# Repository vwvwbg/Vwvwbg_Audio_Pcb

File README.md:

# Vwvwbg_Audio_Pcb
Eagle PCB Project &amp; Gerber

some modified edition for Kevin Gilmore's design and some simple design by me

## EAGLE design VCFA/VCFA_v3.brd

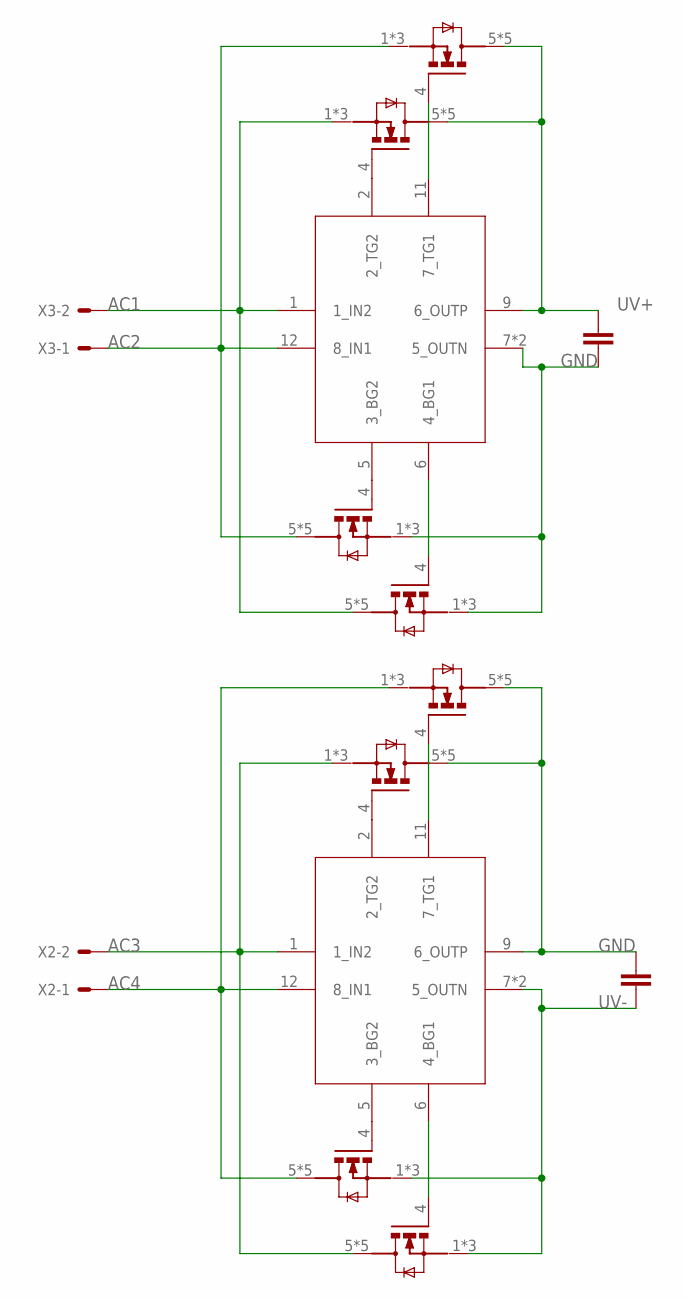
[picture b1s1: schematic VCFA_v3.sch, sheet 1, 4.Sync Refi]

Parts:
C57, C59: 47uF; C1206
Q97, Q98, Q99, Q100, Q105, Q106, Q107, Q108: MOS_SMDTDSON-8; PG-TDSON-8
U$2, U$4: LT4320MSOP; LT4320_MSOP
X2, X3: KK-156-2

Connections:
AC1: Q97.1 (S), Q97.2 (S), Q97.3 (S), Q100.5 (D), Q100.6 (D), Q100.7 (D), Q100.8 (D), Q100.TH (D), U$2.1 (1_IN2), X3.2
AC2: Q98.1 (S), Q98.2 (S), Q98.3 (S), Q99.5 (D), Q99.6 (D), Q99.7 (D), Q99.8 (D), Q99.TH (D), U$2.12 (8_IN1), X3.1
AC3: Q105.1 (S), Q105.2 (S), Q105.3 (S), Q108.5 (D), Q108.6 (D), Q108.7 (D), Q108.8 (D), Q108.TH (D), U$4.1 (1_IN2), X2.2
AC4: Q106.1 (S), Q106.2 (S), Q106.3 (S), Q107.5 (D), Q107.6 (D), Q107.7 (D), Q107.8 (D), Q107.TH (D), U$4.12 (8_IN1), X2.1
GND: C57.2, C59.1, Q99.1 (S), Q99.2 (S), Q99.3 (S), Q100.1 (S), Q100.2 (S), Q100.3 (S), Q105.5 (D), Q105.6 (D), Q105.7 (D), Q105.8 (D), Q105.TH (D), Q106.5 (D), Q106.6 (D), Q106.7 (D), Q106.8 (D), Q106.TH (D), U$2.7 (5_OUTN), U$2.EXP (5_OUTN), U$4.9 (6_OUTP); also elsewhere on the board
unnamed: Q98.4 (G), U$2.11 (7_TG1)
unnamed: Q100.4 (G), U$2.6 (4_BG1)
unnamed: Q97.4 (G), U$2.2 (2_TG2)
unnamed: Q99.4 (G), U$2.5 (3_BG2)
unnamed: Q106.4 (G), U$4.11 (7_TG1)
unnamed: Q108.4 (G), U$4.6 (4_BG1)
unnamed: Q105.4 (G), U$4.2 (2_TG2)
unnamed: Q107.4 (G), U$4.5 (3_BG2)
UV+: C57.1, Q97.5 (D), Q97.6 (D), Q97.7 (D), Q97.8 (D), Q97.TH (D), Q98.5 (D), Q98.6 (D), Q98.7 (D), Q98.8 (D), Q98.TH (D), U$2.9 (6_OUTP); also elsewhere on the board
UV-: C59.2, Q107.1 (S), Q107.2 (S), Q107.3 (S), Q108.1 (S), Q108.2 (S), Q108.3 (S), U$4.7 (5_OUTN), U$4.EXP (5_OUTN); also elsewhere on the board

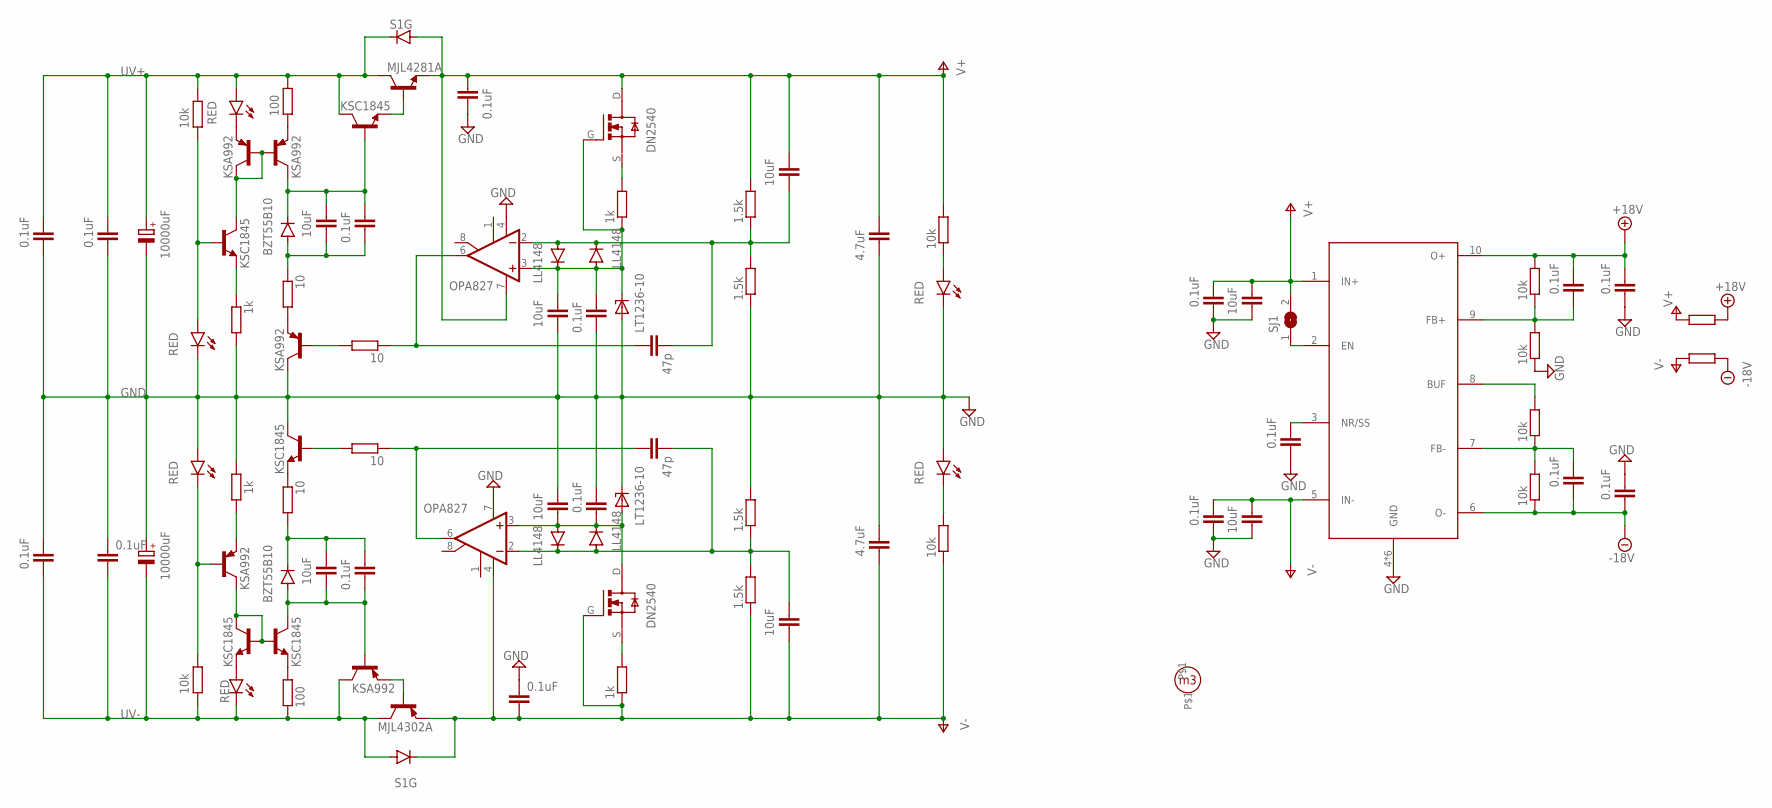
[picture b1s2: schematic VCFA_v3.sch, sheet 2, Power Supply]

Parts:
C2, C43, C44, C45, C46, C49, C50, C67, C68, C69, C70, C71, C72: 0.1uF; C0805
C37, C38: 10000uF; EB35D-8.5
C39, C42, C58, C60: 0.1uF; C050-045X075
C40, C41, C47, C48, C53, C54, C65, C66: 10uF; C1206
C51, C52: 47p; C0805
C55, C56: 4.7uF; C050-075X075
D13, D14: BZT55B10; SOD80C
D15, D16: S1G; DO214AA
D17, D18: LT1236-10; SO8
D19, D20, D21, D22: LL4148; SOD80C
H8: HOLE; M3_HOLE
IC5, IC6: OPA827; SOIC8
LED13, LED14, LED15, LED16, LED17, LED18: RED; LED_SML1206
Q79, Q82, Q84, Q86, Q87: KSC1845; TRANSISTOR_TO92-ECB_N
Q80, Q81, Q83, Q85, Q88: KSA992; TRANSISTOR_TO92-ECB_P
Q89: MJL4281A; TRANSISTOR_TO247_BCE_N
Q90: MJL4302A; TRANSISTOR_TO247_BCE_P
Q91, Q92: DN2540; TRANSISTOR_TO92-SGD_N
R115, R116, R131, R132, R136, R137, R138, R139, R140, R141: 10k; MINI_MELF-0204W
R117, R118, R125, R126: 1k; MINI_MELF-0204W
R119, R122: 100; MINI_MELF-0204W
R120, R121, R123, R124: 10; MINI_MELF-0204W
R127, R128, R129, R130: 1.5k; MINI_MELF-0204W
SJ1: SJ
U$5: TPS7A39WSON10-7A39; SON50P300X300X80-11T165X240N

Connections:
+18V: C69.1, C71.1, R136.2, R141.1, U$5.10 (O+); also elsewhere on the board
-18V: C70.2, C72.2, R139.1, R140.1, U$5.6 (O-); also elsewhere on the board
GND: C2.2, C37.-, C38.+, C39.2, C42.1, C45.1, C46.2, C47.2, C48.1, C49.2, C50.1, C55.1, C56.2, C58.1, C60.2, C65.2, C66.2, C67.2, C68.2, C69.2, C70.1, D17.4 (GND), D18.6 (OUT), IC5.7 (V+), IC6.4 (V-), LED13.C, LED14.A, LED17.C, LED18.A, Q85.C, Q86.C, R117.2, R118.1, R128.1, R129.2, R137.1, U$5.4 (GND), U$5.11 (GND), U$5.12 (GND), U$5.13 (GND), U$5.14 (GND), U$5.15 (GND); also elsewhere on the board
unnamed: Q79.C, Q81.B, Q81.C, Q83.B
unnamed: SJ1.1, U$5.2 (EN)
unnamed: LED15.C, Q81.E
unnamed: Q83.E, R119.2
unnamed: C40.1, C43.1, D13.C, Q83.C, Q87.B
unnamed: C40.2, C43.2, D13.A, R120.1
unnamed: Q85.E, R120.2
unnamed: Q79.E, R117.1
unnamed: LED13.A, Q79.B, R115.2
unnamed: Q80.E, R118.2
unnamed: LED14.C, Q80.B, R116.1
unnamed: Q86.E, R121.1
unnamed: C41.1, C44.1, D14.C, R121.2
unnamed: C41.2, C44.2, D14.A, Q84.C, Q88.B
unnamed: Q80.C, Q82.B, Q82.C, Q84.B
unnamed: Q84.E, R122.1
unnamed: LED16.A, Q82.E
unnamed: Q88.E, Q90.B
unnamed: Q87.E, Q89.B
unnamed: C51.1, IC6.6 (OUT), R123.1
unnamed: C52.1, IC5.6 (OUT), R124.1
unnamed: Q86.B, R124.2
unnamed: Q85.B, R123.2
unnamed: C51.2, C53.2, D19.A, D20.C, IC6.2 (-IN), R127.1, R128.2
unnamed: C47.1, C49.1, D17.6 (OUT), D19.C, D20.A, IC6.3 (+IN), Q91.G, R125.1
unnamed: Q91.S, R125.2
unnamed: C48.2, C50.2, D18.4 (GND), D21.A, D22.C, IC5.3 (+IN), Q92.D
unnamed: Q92.S, R126.2
unnamed: C52.2, C54.1, D21.C, D22.A, IC5.2 (-IN), R129.1, R130.2
unnamed: LED18.C, R132.2
unnamed: LED17.A, R131.1
unnamed: C72.1, R138.1, R139.2, U$5.7 (FB-)
unnamed: R138.2, U$5.8 (BUF)
unnamed: C71.2, R136.1, R137.2, U$5.9 (FB+)
unnamed: C2.1, U$5.3 (NR/SS)
UV+: C37.+, C42.2, C58.2, D15.C, LED15.A, Q87.C, Q89.C, R115.1, R119.1; also elsewhere on the board
UV-: C38.-, C39.1, C60.1, D16.A, LED16.C, Q88.C, Q90.C, R116.2, R122.2; also elsewhere on the board
V+: C45.2, C53.1, C55.2, C66.1, C68.1, D15.A, IC6.7 (V+), Q89.E, Q91.D, R127.2, R131.2, R141.2, SJ1.2, U$5.1 (IN+); also elsewhere on the board
V-: C46.1, C54.2, C56.1, C65.1, C67.1, D16.C, IC5.4 (V-), Q90.E, Q92.G, R126.1, R130.1, R132.1, R140.2, U$5.5 (IN-); also elsewhere on the board

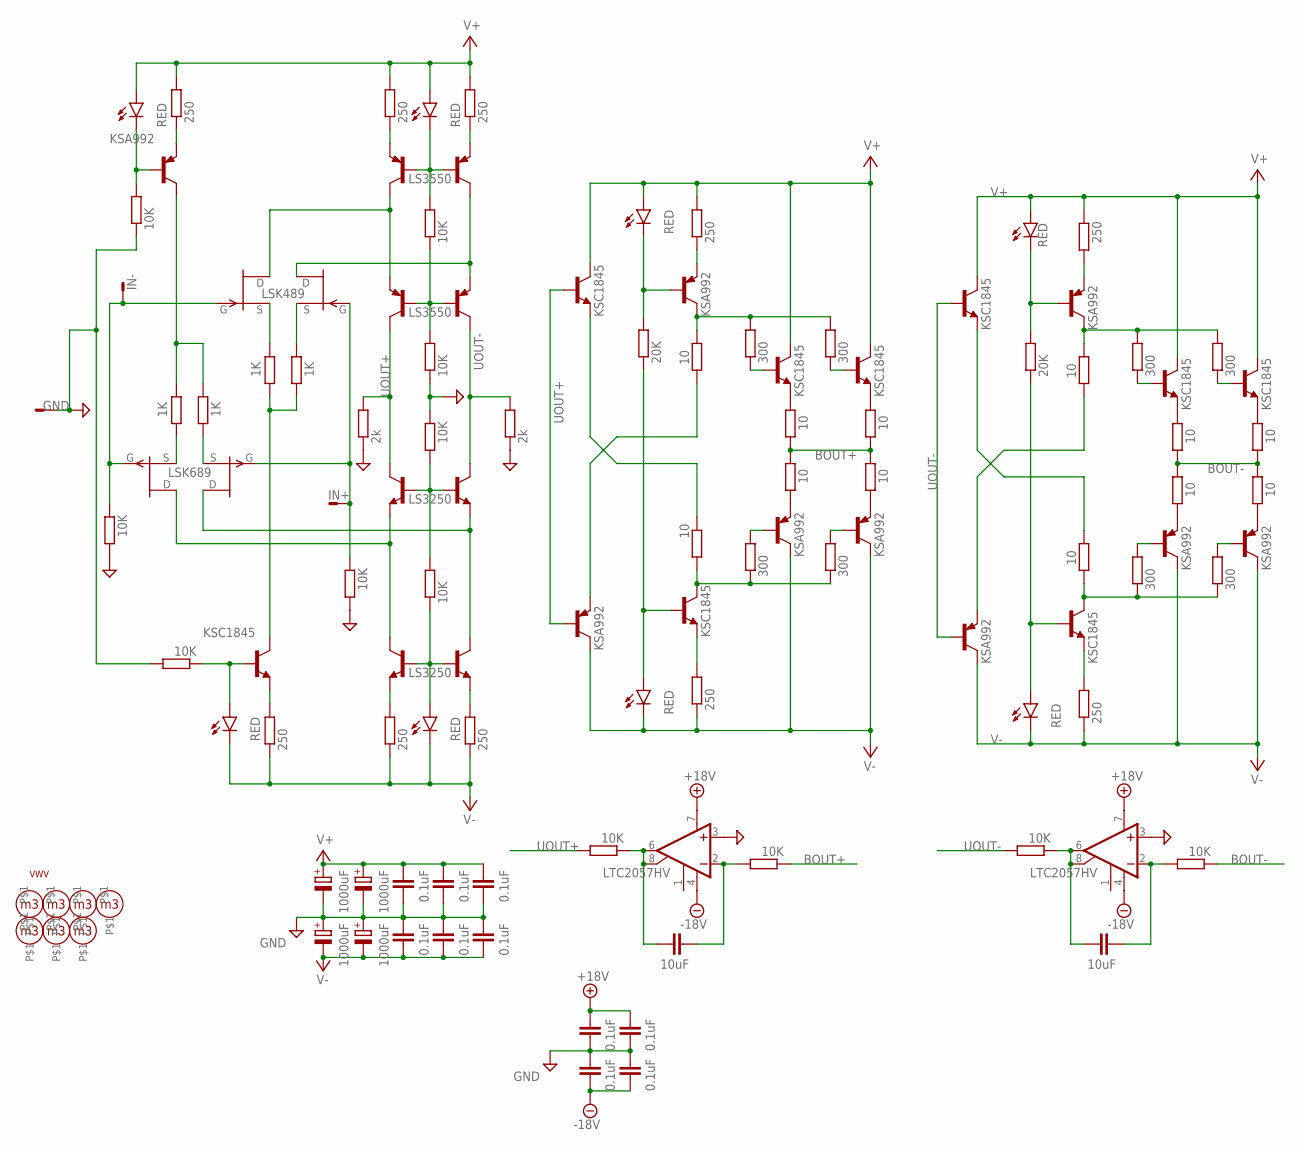
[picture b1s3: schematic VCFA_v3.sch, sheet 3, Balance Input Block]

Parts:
C3, C4, C14, C15: 0.1uF; C0805
C5, C6, C7, C8: 1000uF; E7,5-18
C9, C10, C11, C12, C74, C75: 0.1uF; C050-045X075
C13, C16: 10uF; C1206
H1, H2, H3, H4, H5, H6, H7: HOLE; M3_HOLE
IC1, IC2: LTC2057HV; SOIC8
LED1, LED2, LED3, LED4, LED5, LED6, LED7, LED8: RED; LED_SML1206
Q1: LSK689; SOT-23-6
Q2, Q10, Q11, Q14, Q16, Q18, Q19, Q22, Q24: KSA992; TRANSISTOR_TO92-ECB_P
Q3, Q9, Q12, Q13, Q15, Q17, Q20, Q21, Q23: KSC1845; TRANSISTOR_TO92-ECB_N
Q4: LSK489; SOT-23-6
Q5, Q8: LS3550; SOT-23-6
Q6, Q7: LS3250; SOT-23-6
R3, R4, R14, R15, R16, R17, R21, R29, R36, R44, R134, R135: 10K; MINI_MELF-0204W
R5, R7, R12, R13, R18, R19, R23, R26, R38, R41: 250; MINI_MELF-0204W
R6, R8, R9, R10: 1K; MINI_MELF-0204W
R11, R20: 2k; MINI_MELF-0204W
R22, R37: 20K; MINI_MELF-0204W
R24, R25, R30, R31, R34, R35, R39, R40, R45, R46, R49, R50: 10; MINI_MELF-0204W
R27, R28, R32, R33, R42, R43, R47, R48: 300; MINI_MELF-0204W
S1: VWV
X1: KK-156-3

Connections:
+18V: C3.2, C14.2, IC1.7 (V+), IC2.7 (V+); also elsewhere on the board
-18V: C4.1, C15.1, IC1.4 (V-), IC2.4 (V-); also elsewhere on the board
BOUT+: R29.1, R30.1, R31.2, R34.1, R35.2; also elsewhere on the board
BOUT-: R44.1, R45.1, R46.2, R49.1, R50.2; also elsewhere on the board
GND: C3.1, C4.2, C5.-, C6.+, C7.-, C8.+, C9.2, C10.1, C11.2, C12.1, C14.1, C15.2, C74.2, C75.1, IC1.3 (+IN), IC2.3 (+IN), R3.1, R4.2, R11.1, R15.1, R16.2, R20.1, R134.1, R135.1, X1.2; also elsewhere on the board
IN+: Q1.4 (G), Q4.4 (G), R134.2, X1.3
IN-: Q1.1 (G), Q4.1 (G), R135.2, X1.1
unnamed: Q8.2 (E), R12.1
unnamed: Q10.E, R24.2
unnamed: Q12.E, R26.2
unnamed: Q11.E, R23.1
unnamed: LED5.C, Q11.B, R22.2
unnamed: LED6.A, Q12.B, R22.1
unnamed: Q11.C, R24.1, R27.2, R32.2
unnamed: Q12.C, R25.2, R28.1, R33.1
unnamed: Q9.E, R25.1
unnamed: Q13.B, R27.1
unnamed: Q13.E, R30.2
unnamed: Q16.B, R33.2
unnamed: Q15.B, R32.1
unnamed: Q14.B, R28.2
unnamed: Q14.E, R31.1
unnamed: C13.2, IC1.2 (-IN), R29.2
unnamed: Q15.E, R34.2
unnamed: Q16.E, R35.1
unnamed: C13.1, IC1.6 (OUT), IC1.8 (CMP2), R21.1
unnamed: Q8.5 (E), R18.1
unnamed: Q20.E, R41.2
unnamed: Q19.E, R38.1
unnamed: LED7.C, Q19.B, R37.2
unnamed: LED8.A, Q20.B, R37.1
unnamed: Q19.C, R39.1, R42.2, R47.2
unnamed: Q20.C, R40.2, R43.1, R48.1
unnamed: Q18.E, R39.2
unnamed: Q17.E, R40.1
unnamed: Q21.B, R42.1
unnamed: Q22.B, R43.2
unnamed: Q23.B, R47.1
unnamed: Q24.B, R48.2
unnamed: Q21.E, R45.2
unnamed: Q22.E, R46.1
unnamed: Q23.E, R49.2
unnamed: Q24.E, R50.1
unnamed: C16.2, IC2.2 (-IN), R44.2
unnamed: C16.1, IC2.6 (OUT), IC2.8 (CMP2), R36.1
unnamed: Q7.5 (E), R13.2
unnamed: Q7.2 (E), R19.2
unnamed: Q1.5 (D), Q6.2 (E), Q7.4 (C)
unnamed: Q1.2 (D), Q6.5 (E), Q7.6 (C)
unnamed: LED4.A, Q7.1 (B), Q7.3 (B), R17.1
unnamed: Q6.1 (B), Q6.3 (B), R16.1, R17.2
unnamed: LED2.A, Q3.B, R4.1
unnamed: Q5.1 (B), Q5.3 (B), R14.1, R15.2
unnamed: Q4.2 (D), Q5.5 (E), Q8.4 (C)
unnamed: LED3.C, Q8.1 (B), Q8.3 (B), R14.2
unnamed: Q4.5 (D), Q5.2 (E), Q8.6 (C)
unnamed: LED1.C, Q2.B, R3.2
unnamed: Q2.E, R5.1
unnamed: Q2.C, R6.2, R8.2
unnamed: Q1.6 (S), R8.1
unnamed: Q1.3 (S), R6.1
unnamed: Q4.3 (S), R9.2
unnamed: Q4.6 (S), R10.2
unnamed: Q3.C, R9.1, R10.1
unnamed: Q3.E, R7.2
UOUT+: Q5.6 (C), Q6.6 (C), Q9.B, Q10.B, R11.2, R21.2
UOUT-: Q5.4 (C), Q6.4 (C), Q17.B, Q18.B, R20.2, R36.2
V+: C5.+, C7.+, C9.1, C11.1, C74.1, LED1.A, LED3.A, LED5.A, LED7.A, Q9.C, Q13.C, Q15.C, Q17.C, Q21.C, Q23.C, R5.2, R12.2, R18.2, R23.2, R38.2; also elsewhere on the board
V-: C6.-, C8.-, C10.2, C12.2, C75.2, LED2.C, LED4.C, LED6.C, LED8.C, Q10.C, Q14.C, Q16.C, Q18.C, Q22.C, Q24.C, R7.1, R13.1, R19.1, R26.1, R41.1; also elsewhere on the board

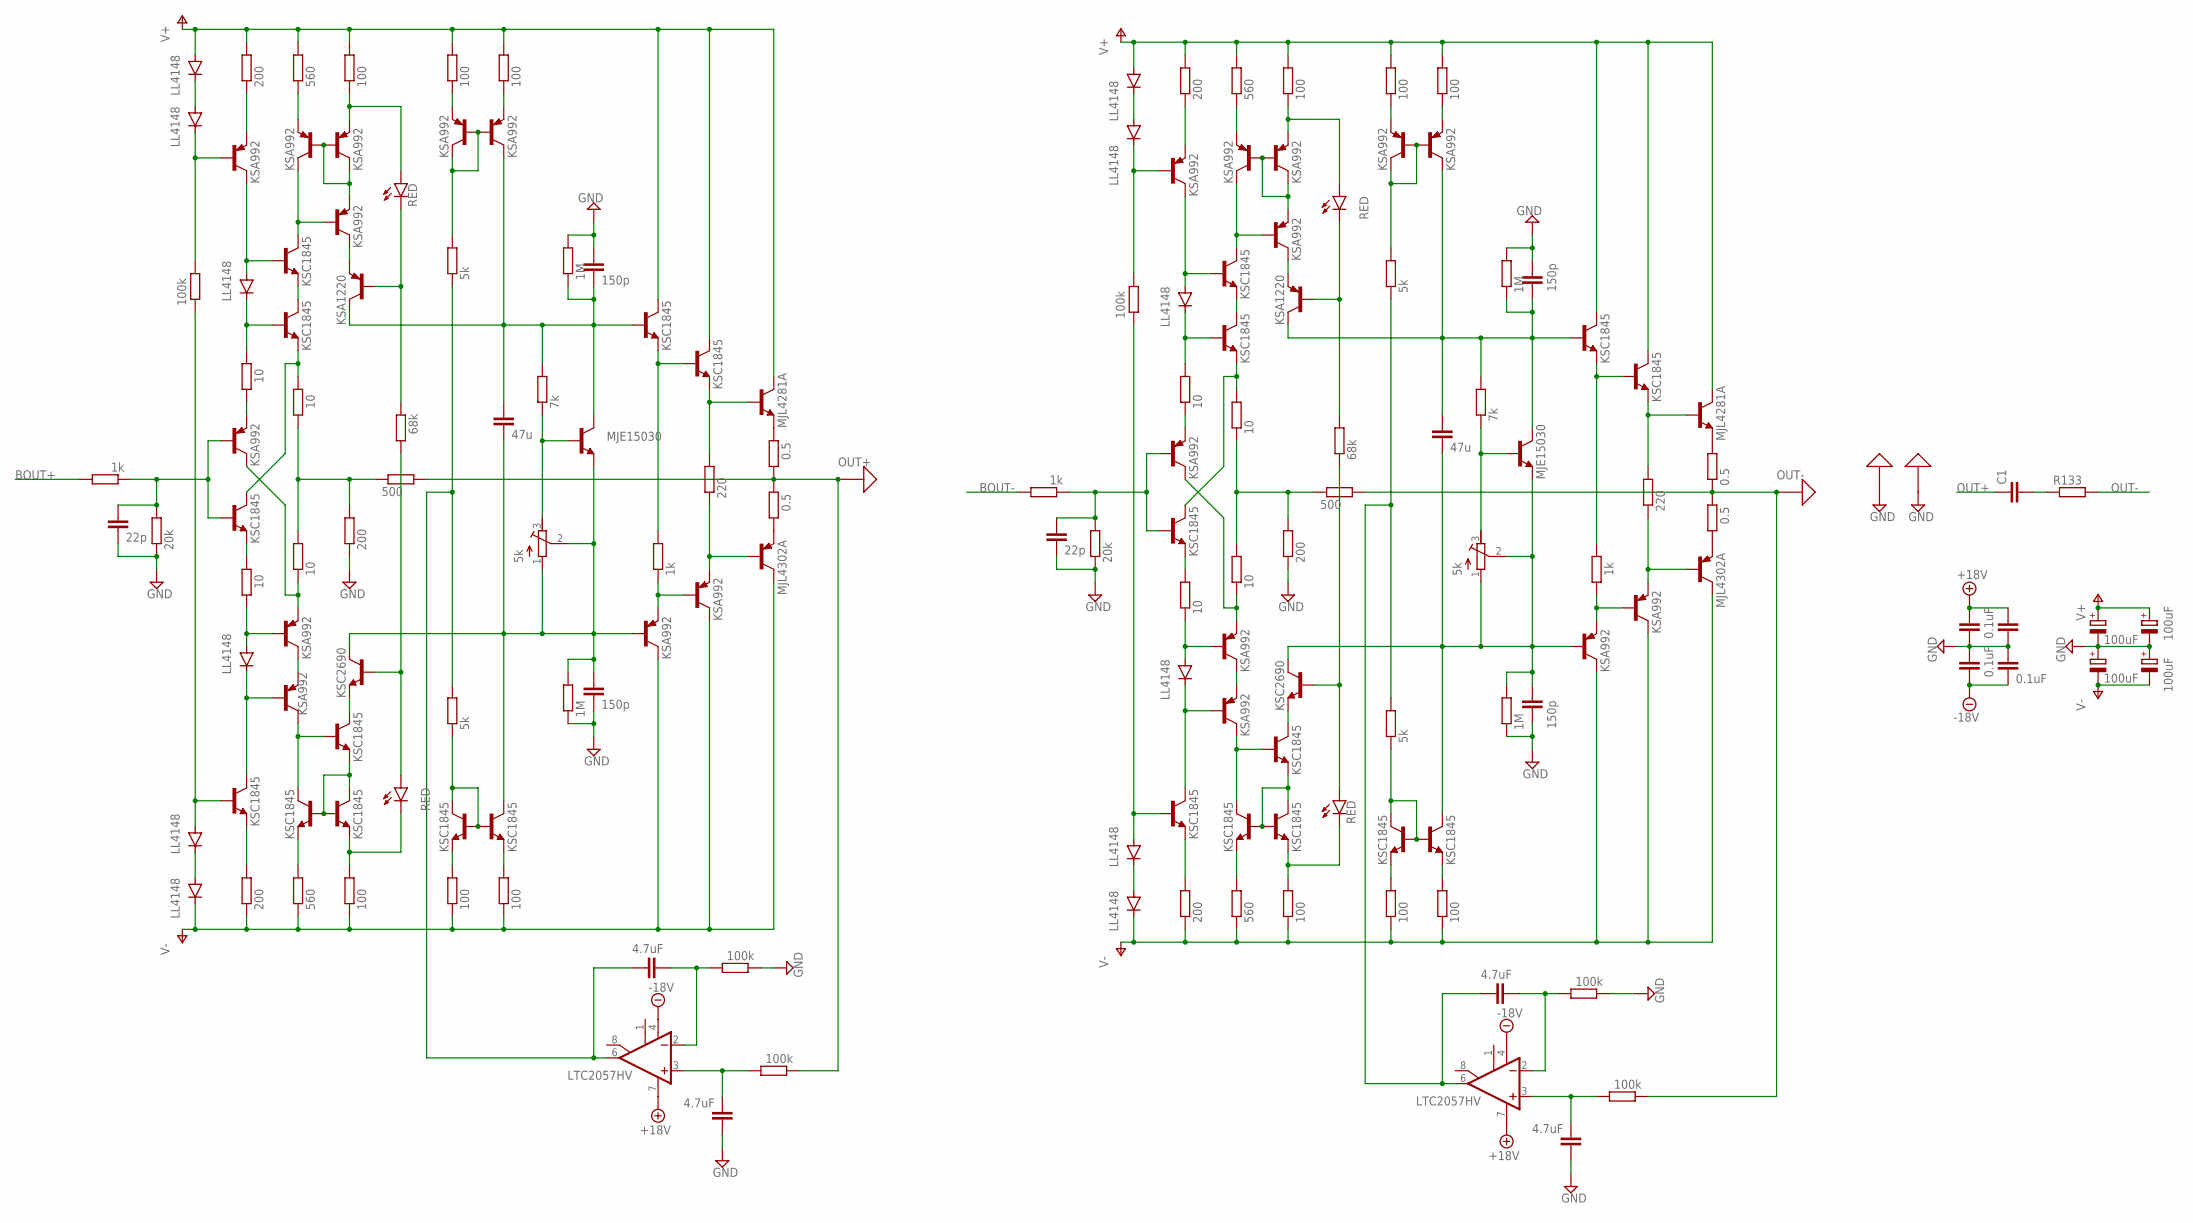
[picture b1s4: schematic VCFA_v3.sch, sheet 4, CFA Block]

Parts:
C1: C-EUECWU-V; ECHU-Y
C17, C27: 22p; C0805
C18, C28: 47u; C1210
C19, C20, C29, C30: 150p; C0805
C21, C22, C31, C32: 4.7uF; C1210
C23, C24, C33, C34: 0.1uF; C0603K
C25, C26, C35, C36: 100uF; E5-8,5
D1, D2, D3, D4, D5, D6, D7, D8, D9, D10, D11, D12: LL4148; SOD80C
IC3, IC4: LTC2057HV; SOIC8
LED9, LED10, LED11, LED12: RED; LED_SML1206
PAD1, PAD2, PAD3, PAD4: PAD; PAD-16
Q25, Q26, Q31, Q32, Q33, Q35, Q36, Q41, Q43, Q47, Q49, Q52, Q53, Q58, Q59, Q60, Q62, Q63, Q68, Q70, Q74, Q76: KSA992; TRANSISTOR_TO92-ECB_P
Q27, Q28, Q29, Q30, Q34, Q37, Q38, Q42, Q44, Q46, Q48, Q54, Q55, Q56, Q57, Q61, Q64, Q65, Q69, Q71, Q73, Q75: KSC1845; TRANSISTOR_TO92-ECB_N
Q39, Q66: KSA1220; TRANSISTOR_TO126_P
Q40, Q67: KSC2690; TRANSISTOR_TO126_N
Q45, Q72: MJE15030; TRANSISTOR_TO220_BCE_N
Q50, Q77: MJL4281A; TRANSISTOR_TO247_BCE_N
Q51, Q78: MJL4302A; TRANSISTOR_TO247_BCE_P
R51, R77, R83, R109: 1k; MINI_MELF-0204W
R52, R84: 20k; MINI_MELF-0204W
R53, R79, R82, R85, R111, R114: 100k; MINI_MELF-0204W
R54, R57, R63, R86, R89, R95: 200; MINI_MELF-0204W
R55, R56, R59, R60, R87, R88, R91, R92: 10; MINI_MELF-0204W
R58, R61, R90, R93: 560; MINI_MELF-0204W
R62, R64, R67, R70, R71, R72, R94, R96, R99, R102, R103, R104: 100; MINI_MELF-0204W
R65, R97: 68k; MINI_MELF-0204W
R66, R98: 500; MINI_MELF-0204W
R68, R69, R100, R101: 5k; MINI_MELF-0204W
R73, R105: 7k; MINI_MELF-0204W
R74, R106: 5k; RTRIM3296W
R75, R76, R107, R108: 1M; MINI_MELF-0204W
R78, R110: 220; MINI_MELF-0204W
R80, R81, R112, R113: 0.5; R2512
R133: R-EU_R2512; R2512

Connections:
+18V: C23.1, C33.1, IC3.7 (V+), IC4.7 (V+); also elsewhere on the board
-18V: C24.2, C34.2, IC3.4 (V-), IC4.4 (V-); also elsewhere on the board
BOUT+: R51.2; also elsewhere on the board
BOUT-: R83.2; also elsewhere on the board
GND: C17.2, C19.1, C20.2, C22.1, C23.2, C24.1, C25.-, C26.+, C27.2, C29.1, C30.2, C32.1, C33.2, C34.1, C35.-, C36.+, PAD3.P$1, PAD4.P$1, R52.1, R63.1, R75.2, R76.1, R79.1, R84.1, R95.1, R107.2, R108.1, R111.1; also elsewhere on the board
unnamed: Q25.E, R54.1
unnamed: D5.A, Q25.C, Q29.B
unnamed: D1.C, D2.A
unnamed: D2.C, Q25.B, R53.2
unnamed: D5.C, Q30.B, R55.2
unnamed: Q29.E, Q30.C
unnamed: Q27.C, Q30.E, R59.2
unnamed: R59.1, R60.2, R63.2, R66.1
unnamed: Q26.C, Q31.E, R60.1
unnamed: D6.A, Q31.B, R56.1
unnamed: D6.C, Q28.C, Q32.B
unnamed: Q28.E, R57.2
unnamed: D3.C, D4.A
unnamed: Q31.C, Q32.E
unnamed: Q26.E, R55.1
unnamed: Q27.E, R56.2
unnamed: C17.1, Q26.B, Q27.B, R51.1, R52.2
unnamed: Q29.C, Q33.C, Q36.B
unnamed: Q33.B, Q35.B, Q35.C, Q36.E
unnamed: Q33.E, R58.1
unnamed: LED9.A, Q35.E, R62.1
unnamed: Q36.C, Q39.E
unnamed: LED9.C, Q39.B, R65.2
unnamed: Q34.B, Q37.E, Q38.B, Q38.C
unnamed: LED10.C, Q38.E, R64.2
unnamed: Q34.E, R61.2
unnamed: Q32.C, Q34.C, Q37.B
unnamed: Q37.C, Q40.E
unnamed: LED10.A, Q40.B, R65.1
unnamed: C18.1, C19.2, Q39.C, Q43.C, Q45.C, Q46.B, R73.2, R75.1
unnamed: Q41.B, Q41.C, Q43.B, R68.2
unnamed: Q42.B, Q42.C, Q44.B, R69.1
unnamed: Q41.E, R67.1
unnamed: Q43.E, R71.1
unnamed: Q42.E, R70.2
unnamed: Q44.E, R72.2
unnamed: Q46.E, Q48.B, R77.2
unnamed: Q47.E, Q49.B, R77.1
unnamed: C18.2, C20.1, Q40.C, Q44.C, Q45.E, Q47.B, R74.1 (A), R74.2 (S), R76.2
unnamed: Q48.E, Q50.B, R78.2
unnamed: Q49.E, Q51.B, R78.1
unnamed: Q50.E, R80.2
unnamed: Q51.E, R81.1
unnamed: C21.2, IC3.2 (-IN), R79.2
unnamed: C22.2, IC3.3 (+IN), R82.2
unnamed: D3.A, Q28.B, R53.1
unnamed: Q45.B, R73.1, R74.3 (E)
unnamed: C21.1, IC3.6 (OUT), R68.1, R69.2
unnamed: C1.2, R133.1
unnamed: Q52.E, R86.1
unnamed: D11.A, Q52.C, Q56.B
unnamed: D7.C, D8.A
unnamed: D8.C, Q52.B, R85.2
unnamed: D11.C, Q57.B, R87.2
unnamed: Q56.E, Q57.C
unnamed: Q54.C, Q57.E, R91.2
unnamed: R91.1, R92.2, R95.2, R98.1
unnamed: Q53.C, Q58.E, R92.1
unnamed: D12.A, Q58.B, R88.1
unnamed: D12.C, Q55.C, Q59.B
unnamed: Q55.E, R89.2
unnamed: D9.C, D10.A
unnamed: Q58.C, Q59.E
unnamed: Q53.E, R87.1
unnamed: Q54.E, R88.2
unnamed: C27.1, Q53.B, Q54.B, R83.1, R84.2
unnamed: Q56.C, Q60.C, Q63.B
unnamed: Q60.B, Q62.B, Q62.C, Q63.E
unnamed: Q60.E, R90.1
unnamed: LED11.A, Q62.E, R94.1
unnamed: Q63.C, Q66.E
unnamed: LED11.C, Q66.B, R97.2
unnamed: Q61.B, Q64.E, Q65.B, Q65.C
unnamed: LED12.C, Q65.E, R96.2
unnamed: Q61.E, R93.2
unnamed: Q59.C, Q61.C, Q64.B
unnamed: Q64.C, Q67.E
unnamed: LED12.A, Q67.B, R97.1
unnamed: C28.1, C29.2, Q66.C, Q70.C, Q72.C, Q73.B, R105.2, R107.1
unnamed: Q68.B, Q68.C, Q70.B, R100.2
unnamed: Q69.B, Q69.C, Q71.B, R101.1
unnamed: Q68.E, R99.1
unnamed: Q70.E, R103.1
unnamed: Q69.E, R102.2
unnamed: Q71.E, R104.2
unnamed: Q73.E, Q75.B, R109.2
unnamed: Q74.E, Q76.B, R109.1
unnamed: C28.2, C30.1, Q67.C, Q71.C, Q72.E, Q74.B, R106.1 (A), R106.2 (S), R108.2
unnamed: Q75.E, Q77.B, R110.2
unnamed: Q76.E, Q78.B, R110.1
unnamed: Q77.E, R112.2
unnamed: Q78.E, R113.1
unnamed: C31.2, IC4.2 (-IN), R111.2
unnamed: C32.2, IC4.3 (+IN), R114.2
unnamed: D9.A, Q55.B, R85.1
unnamed: Q72.B, R105.1, R106.3 (E)
unnamed: C31.1, IC4.6 (OUT), R100.1, R101.2
OUT+: C1.1, PAD1.P$1, R66.2, R80.1, R81.2, R82.1
OUT-: PAD2.P$1, R98.2, R112.1, R113.2, R114.1, R133.2
V+: C25.+, C35.+, D1.A, D7.A, Q46.C, Q48.C, Q50.C, Q73.C, Q75.C, Q77.C, R54.2, R58.2, R62.2, R67.2, R71.2, R86.2, R90.2, R94.2, R99.2, R103.2; also elsewhere on the board
V-: C26.-, C36.-, D4.C, D10.C, Q47.C, Q49.C, Q51.C, Q74.C, Q76.C, Q78.C, R57.1, R61.1, R64.1, R70.1, R72.1, R89.1, R93.1, R96.1, R102.1, R104.1; also elsewhere on the board

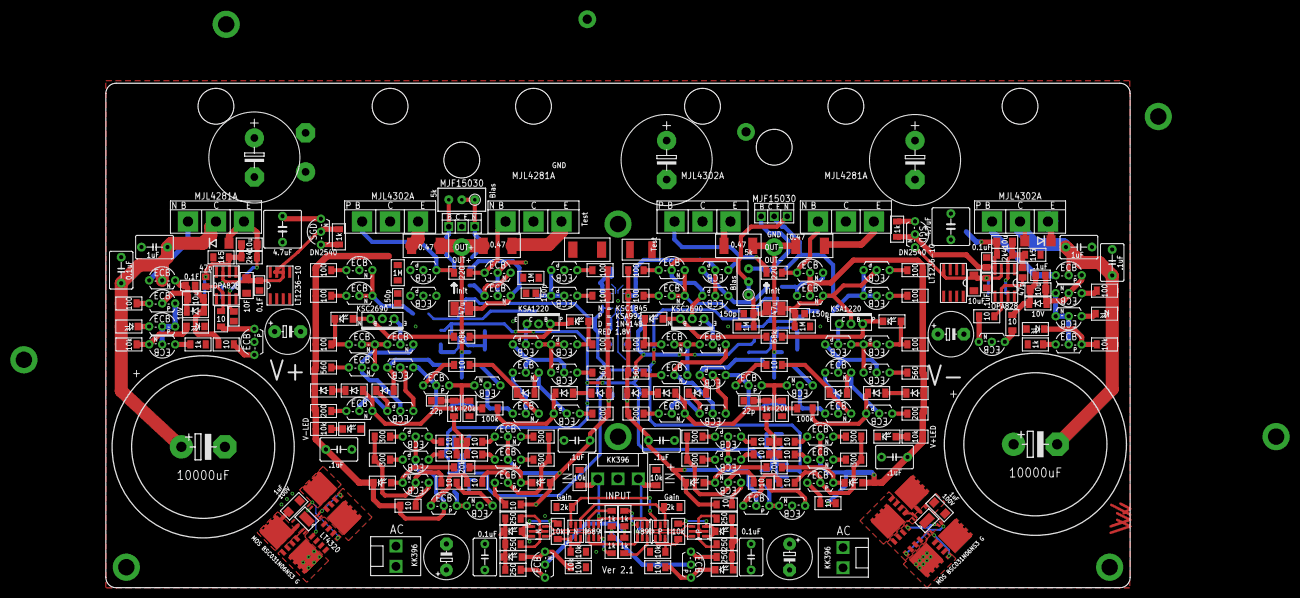
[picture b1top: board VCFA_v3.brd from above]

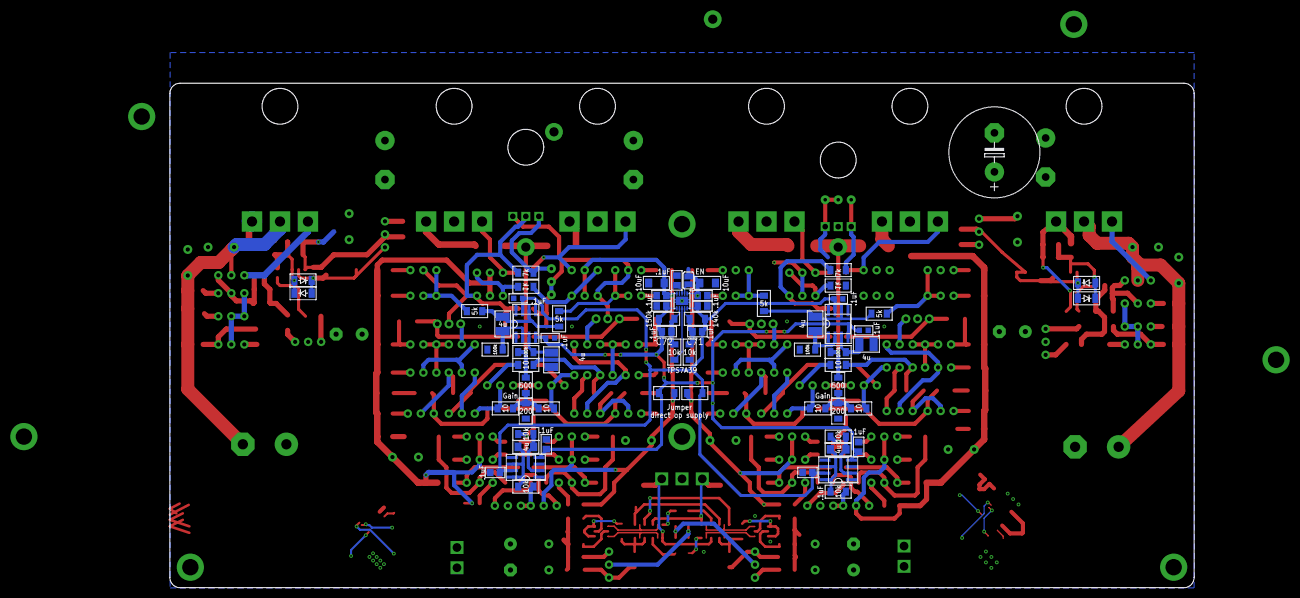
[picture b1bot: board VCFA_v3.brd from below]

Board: 2 copper layers, 200.0 x 98.5 mm, 375 parts (66 on the bottom side), 217 nets.

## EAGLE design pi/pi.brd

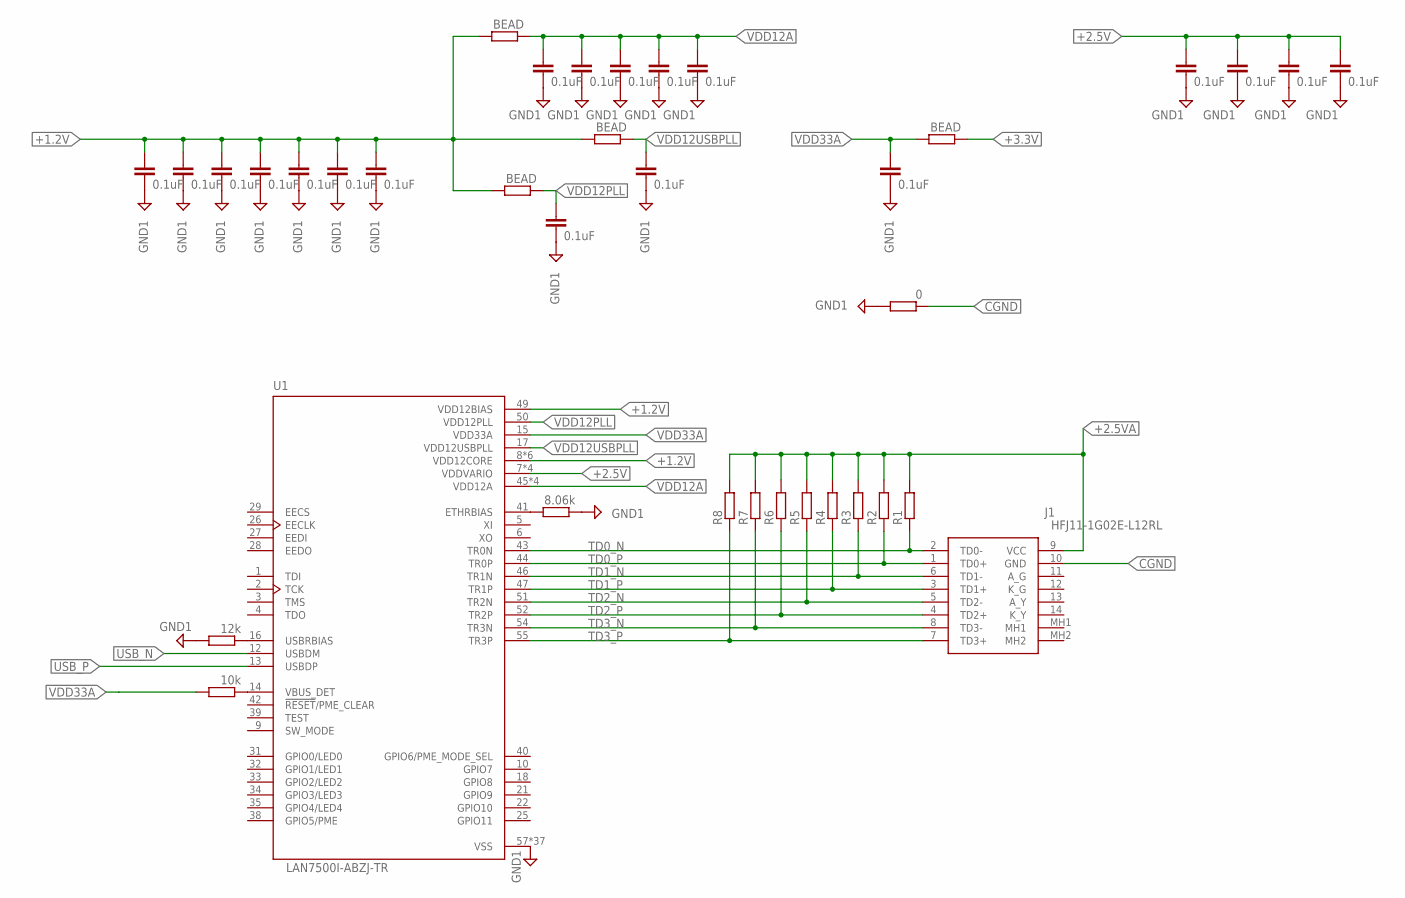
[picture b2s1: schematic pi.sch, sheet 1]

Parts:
C1, C2, C3, C4, C5, C6, C7, C8, C9, C10, C11, C12, C13, C14, C15, C16, C17, C18, C19: 0.1uF; C0603K
J1: HFJ11-1G02E-L12RL; HFJ111G02EL12RL
R1, R2, R3, R4, R5, R6, R7, R8: R-EU_MELF0204R; MINI_MELF-0204R
R9: 8.06k; MINI_MELF-0204R
R10: 12k; MINI_MELF-0204R
R11: 10k; MINI_MELF-0204R
R12, R13, R14, R16: BEAD; MINI_MELF-0204R
R15: 0; MINI_MELF-0204R
U1: LAN7500I-ABZJ-TR; QFN50P800X800X100-57N

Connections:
+1.2V: C4.1, C5.1, C6.1, C7.1, C8.1, C9.1, C19.1, R12.2, R13.2, R16.2, U1.8 (VDD12CORE), U1.11 (VDD12CORE), U1.20 (VDD12CORE), U1.23 (VDD12CORE), U1.30 (VDD12CORE), U1.36 (VDD12CORE), U1.49 (VDD12BIAS)
+2.5V: C15.1, C16.1, C17.1, C18.1, U1.7 (VDDVARIO), U1.19 (VDDVARIO), U1.24 (VDDVARIO), U1.37 (VDDVARIO)
+2.5VA: J1.9 (VCC), R1.2, R2.2, R3.2, R4.2, R5.2, R6.2, R7.2, R8.2
+3.3V: R14.1
CGND: J1.10 (GND), R15.1
GND1: C1.2, C2.2, C3.2, C4.2, C5.2, C6.2, C7.2, C8.2, C9.2, C10.2, C11.2, C12.2, C13.2, C14.2, C15.2, C16.2, C17.2, C18.2, C19.2, R9.1, R10.2, R15.2, U1.57 (VSS), U1.V1 (VSS), U1.V2 (VSS), U1.V3 (VSS), U1.V4 (VSS), U1.V5 (VSS), U1.V6 (VSS), U1.V7 (VSS), U1.V8 (VSS), U1.V9 (VSS), U1.V10 (VSS), U1.V11 (VSS), U1.V12 (VSS), U1.V13 (VSS), U1.V14 (VSS), U1.V15 (VSS), U1.V16 (VSS), U1.V17 (VSS), U1.V18 (VSS), U1.V19 (VSS), U1.V20 (VSS), U1.V21 (VSS), U1.V22 (VSS), U1.V23 (VSS), U1.V24 (VSS), U1.V25 (VSS), U1.V26 (VSS), U1.V27 (VSS), U1.V28 (VSS), U1.V29 (VSS), U1.V30 (VSS), U1.V31 (VSS), U1.V32 (VSS), U1.V33 (VSS), U1.V34 (VSS), U1.V35 (VSS), U1.V36 (VSS)
unnamed: R9.2, U1.41 (ETHRBIAS)
unnamed: R10.1, U1.16 (USBRBIAS)
unnamed: R11.1, U1.14 (VBUS_DET)
TD0_N: J1.2 (TD0-), R1.1, U1.43 (TR0N)
TD0_P: J1.1 (TD0+), R2.1, U1.44 (TR0P)
TD1_N: J1.6 (TD1-), R3.1, U1.46 (TR1N)
TD1_P: J1.3 (TD1+), R4.1, U1.47 (TR1P)
TD2_N: J1.5 (TD2-), R5.1, U1.51 (TR2N)
TD2_P: J1.4 (TD2+), R6.1, U1.52 (TR2P)
TD3_N: J1.8 (TD3-), R7.1, U1.54 (TR3N)
TD3_P: J1.7 (TD3+), R8.1, U1.55 (TR3P)
USB_N: U1.12 (USBDM); also elsewhere on the board
USB_P: U1.13 (USBDP); also elsewhere on the board
VDD12A: C10.1, C11.1, C12.1, C13.1, C14.1, R16.1, U1.45 (VDD12A), U1.48 (VDD12A), U1.53 (VDD12A), U1.56 (VDD12A)
VDD12PLL: C2.1, R13.1, U1.50 (VDD12PLL)
VDD12USBPLL: C1.1, R12.1, U1.17 (VDD12USBPLL)
VDD33A: C3.1, R11.2, R14.2, U1.15 (VDD33A)

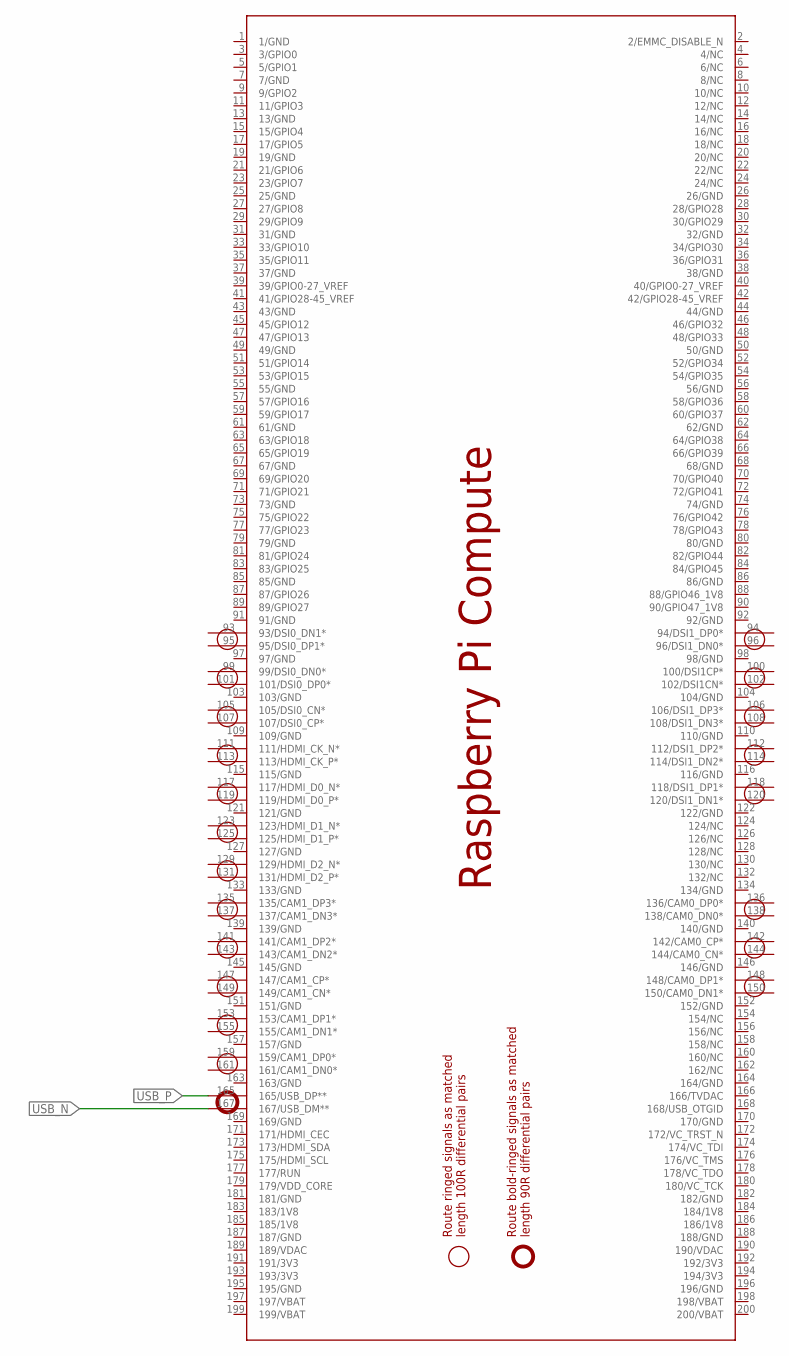
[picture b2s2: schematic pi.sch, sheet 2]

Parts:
PCB1: RPI_COMPUTE

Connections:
USB_N: PCB1.167 (167/USB_DM**); also elsewhere on the board
USB_P: PCB1.165 (165/USB_DP**); also elsewhere on the board

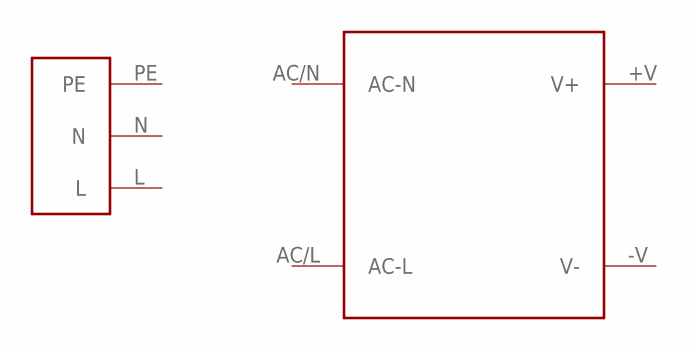
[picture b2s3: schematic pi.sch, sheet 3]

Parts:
U$1: DD21; DD21.NOCOVER
U$2: IRM-15-5; IRM-15

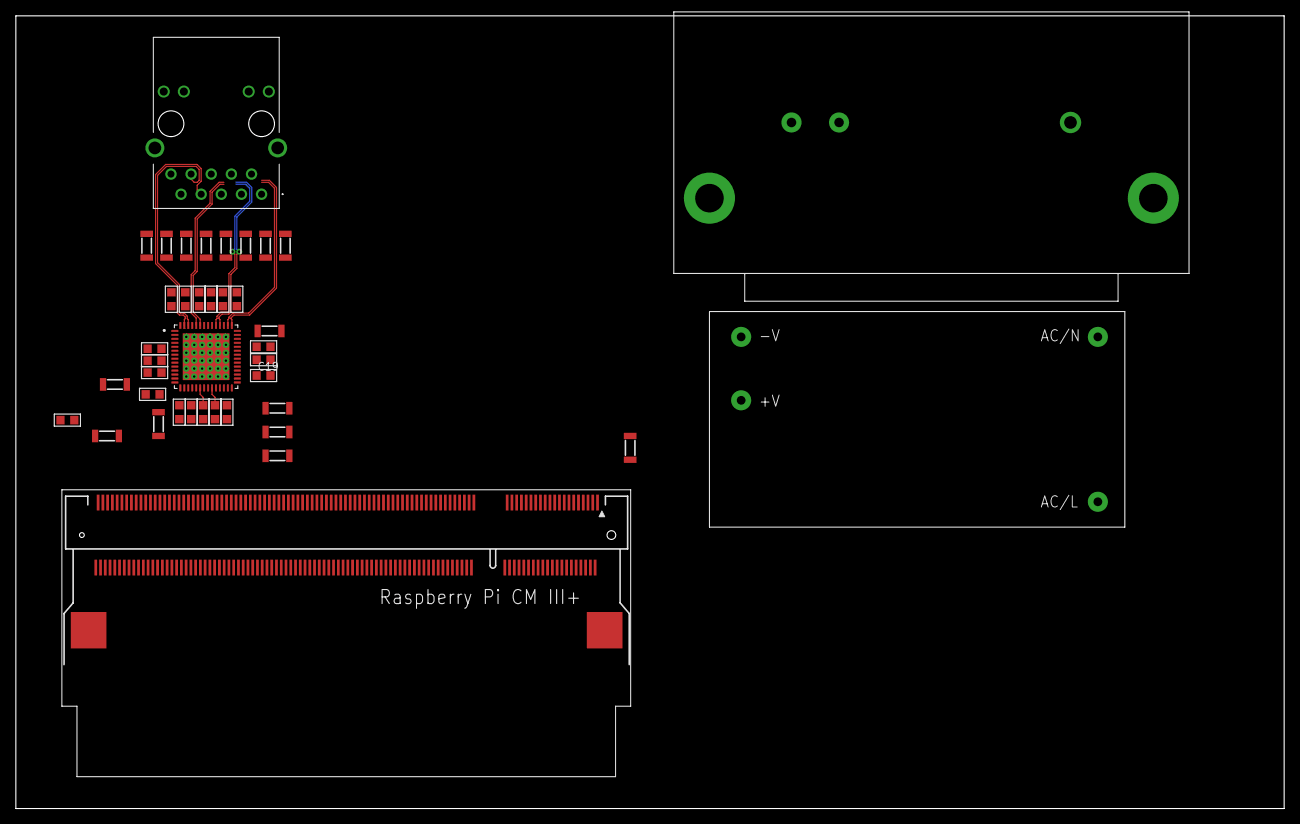
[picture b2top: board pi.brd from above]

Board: 2 copper layers, 160.0 x 100.0 mm, 40 parts (0 on the bottom side), 22 nets.
